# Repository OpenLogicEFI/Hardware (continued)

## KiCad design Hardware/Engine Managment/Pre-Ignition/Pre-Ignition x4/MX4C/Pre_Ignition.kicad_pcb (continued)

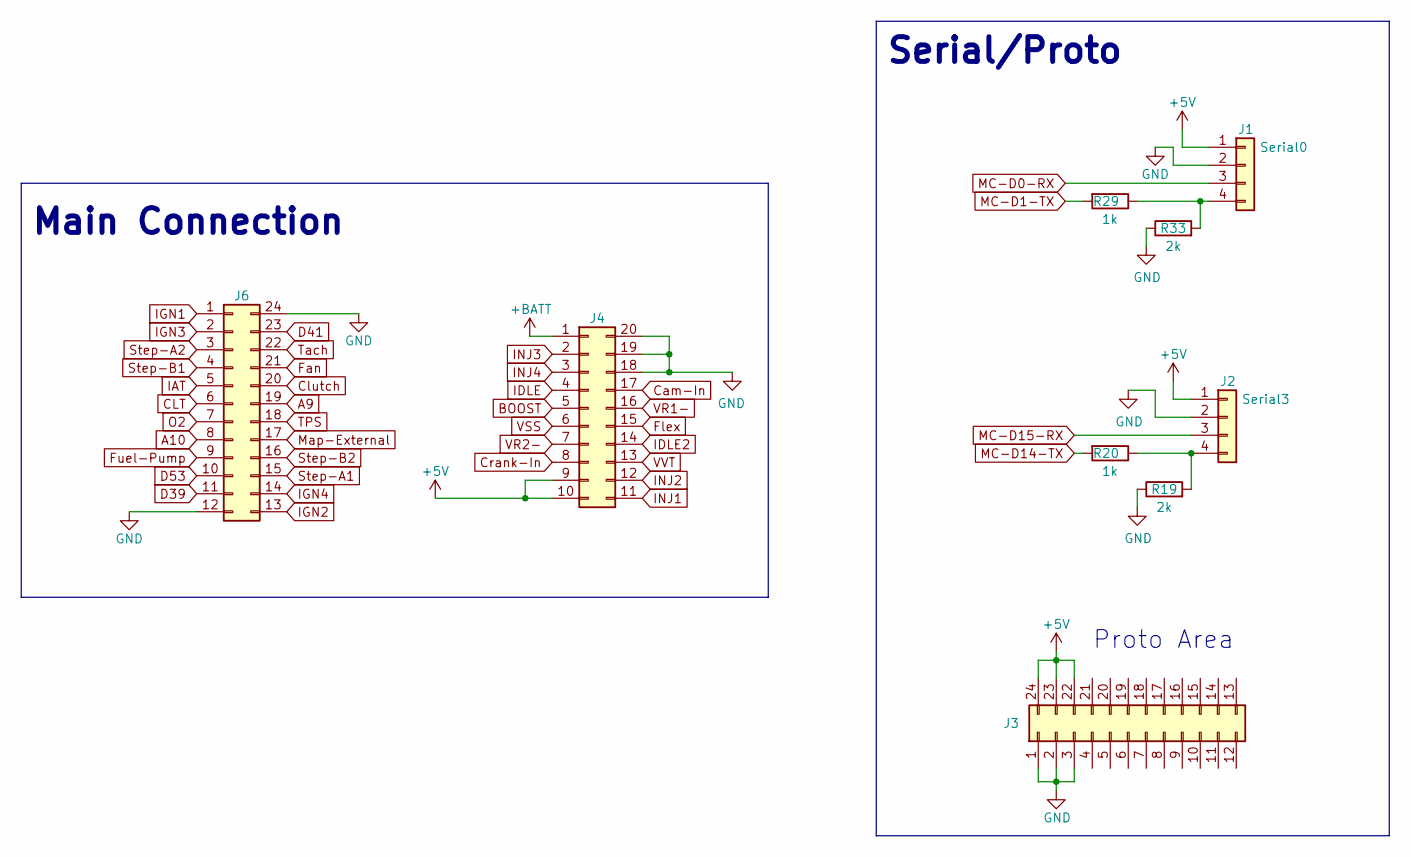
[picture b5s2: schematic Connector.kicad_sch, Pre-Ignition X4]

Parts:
J1: Serial0; 1X4-PROTO
J2: Serial3; 1X4-PROTO
J3: Conn_02x12_Counter_Clockwise; PROTO-3X8-24pin
J4: Conn_02x10_Counter_Clockwise; Molex_Micro-Fit_3.0_43045-2000_2x10_P3.00mm_Horizontal
J6: Conn_02x12_Counter_Clockwise; Molex_Micro-Fit_3.0_43045-2400_2x12_P3.00mm_Horizontal
R19, R33: 2k; R_0603_1608Metric; LCSC C22975
R20, R29: 1k; R_0603_1608Metric; LCSC C21190

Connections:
A9: J6.19; also elsewhere on the board
A10: J6.8; also elsewhere on the board
BOOST: J4.5; also elsewhere on the board
CLT: J6.6; also elsewhere on the board
Cam-In: J4.17; also elsewhere on the board
Clutch: J6.20; also elsewhere on the board
Crank-In: J4.8; also elsewhere on the board
D39: J6.11; also elsewhere on the board
D41: J6.23; also elsewhere on the board
D53: J6.10; also elsewhere on the board
Fan: J6.21; also elsewhere on the board
Flex: J4.15; also elsewhere on the board
Fuel-Pump: J6.9; also elsewhere on the board
IAT: J6.5; also elsewhere on the board
IDLE: J4.4; also elsewhere on the board
IDLE2: J4.14; also elsewhere on the board
IGN1: J6.1; also elsewhere on the board
IGN2: J6.13; also elsewhere on the board
IGN3: J6.2; also elsewhere on the board
IGN4: J6.14; also elsewhere on the board
INJ1: J4.11; also elsewhere on the board
INJ2: J4.12; also elsewhere on the board
INJ3: J4.2; also elsewhere on the board
INJ4: J4.3; also elsewhere on the board
MC-D0-RX: J1.3; also elsewhere on the board
MC-D1-TX: R29.2; also elsewhere on the board
MC-D14-TX: R20.2; also elsewhere on the board
MC-D15-RX: J2.3; also elsewhere on the board
Map-External: J6.17; also elsewhere on the board
unnamed: J1.4, R29.1, R33.2
unnamed: J2.4, R19.2, R20.1
O2: J6.7; also elsewhere on the board
Step-A1: J6.15; also elsewhere on the board
Step-A2: J6.3; also elsewhere on the board
Step-B1: J6.4; also elsewhere on the board
Step-B2: J6.16; also elsewhere on the board
TPS: J6.18; also elsewhere on the board
Tach: J6.22; also elsewhere on the board
VR1-: J4.16; also elsewhere on the board
VR2-: J4.7; also elsewhere on the board
VSS: J4.6; also elsewhere on the board

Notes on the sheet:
Proto Area
Serial/Proto
Main Connection

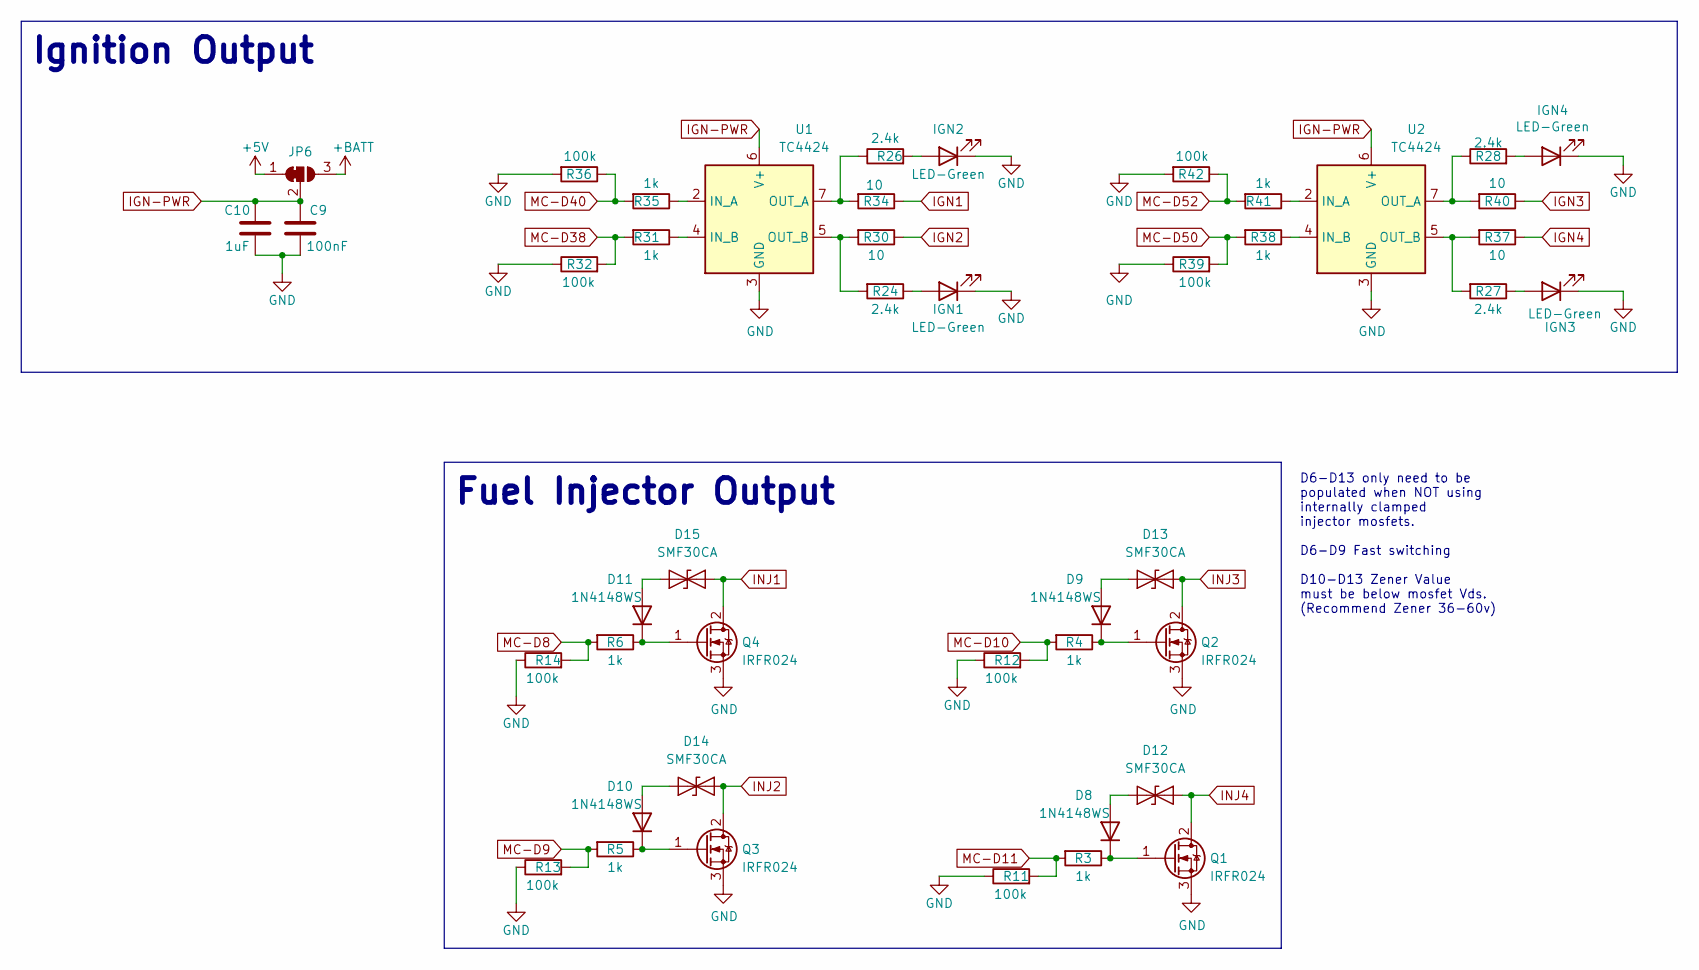
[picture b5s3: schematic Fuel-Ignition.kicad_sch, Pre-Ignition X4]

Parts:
C9: 100nF; C_0603_1608Metric; JLC C14663
C10: 1uF; C_0603_1608Metric; JLC C15849
D8, D9, D10, D11: 1N4148WS; D_SOD-323F; LCSC C2128
D12, D13, D14, D15: SMF30CA; D_SOD-123F
IGN1, IGN2, IGN3, IGN4: LED-Green; LED_0603_1608Metric; JLC C2286
JP6: SolderJumper_3_Bridged12; SolderJumper-3_P1.3mm_Bridged12_RoundedPad1.0x1.5mm_NumberL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
Q1, Q2, Q3, Q4: IRFR024; TO-252-2; LCSC C2583
R3, R4, R5, R6, R31, R35, R38, R41: 1k; R_0603_1608Metric; JLC C21190
R11, R12, R13, R14, R32, R36, R39, R42: 100k; R_0603_1608Metric; JLC C25803
R24, R27, R28: 2.4k; R_0603_1608Metric; JLC C22940
R26: 2.4k; R_0603_1608Metric; LCSC C22940
R30, R34, R37, R40: 10; R_1206_3216Metric; JLC C17561
U1, U2: TC4424; SOIC-8_3.9x4.9mm_P1.27mm; LCSC C2685358

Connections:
IGN1: R34.1; also elsewhere on the board
IGN2: R30.1; also elsewhere on the board
IGN3: R40.1; also elsewhere on the board
IGN4: R37.1; also elsewhere on the board
IGN-PWR: C9.1, C10.1, JP6.2 (C), U1.6 (V+), U2.6 (V+)
INJ1: D15.1 (A1), Q4.2 (D); also elsewhere on the board
INJ2: D14.1 (A1), Q3.2 (D); also elsewhere on the board
INJ3: D13.1 (A1), Q2.2 (D); also elsewhere on the board
INJ4: D12.1 (A1), Q1.2 (D); also elsewhere on the board
MC-D8: R6.2, R14.2; also elsewhere on the board
MC-D9: R5.2, R13.2; also elsewhere on the board
MC-D10: R4.2, R12.2; also elsewhere on the board
MC-D11: R3.2, R11.2; also elsewhere on the board
MC-D38: R31.2, R32.2; also elsewhere on the board
MC-D40: R35.2, R36.1; also elsewhere on the board
MC-D50: R38.2, R39.2; also elsewhere on the board
MC-D52: R41.2, R42.1; also elsewhere on the board
unnamed: D8.1 (K), Q1.1 (G), R3.1
unnamed: D9.1 (K), Q2.1 (G), R4.1
unnamed: D10.2 (A), D14.2 (A2)
unnamed: D10.1 (K), Q3.1 (G), R5.1
unnamed: D11.2 (A), D15.2 (A2)
unnamed: D11.1 (K), Q4.1 (G), R6.1
unnamed: D8.2 (A), D12.2 (A2)
unnamed: D9.2 (A), D13.2 (A2)
unnamed: IGN1.2 (A), R24.1
unnamed: IGN2.2 (A), R26.2
unnamed: IGN3.2 (A), R27.1
unnamed: IGN4.2 (A), R28.2
unnamed: R35.1, U1.2 (IN_A)
unnamed: R31.1, U1.4 (IN_B)
unnamed: R26.1, R34.2, U1.7 (OUT_A)
unnamed: R24.2, R30.2, U1.5 (OUT_B)
unnamed: R41.1, U2.2 (IN_A)
unnamed: R38.1, U2.4 (IN_B)
unnamed: R28.1, R40.2, U2.7 (OUT_A)
unnamed: R27.2, R37.2, U2.5 (OUT_B)

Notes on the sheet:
Fuel Injector Output
D6-D13 only need to be populated when NOT using internally clamped injector mosfets. D6-D9 Fast switching D10-D13 Zener Value must be below mosfet Vds. (Recommend Zener 36-60v)
Ignition Output

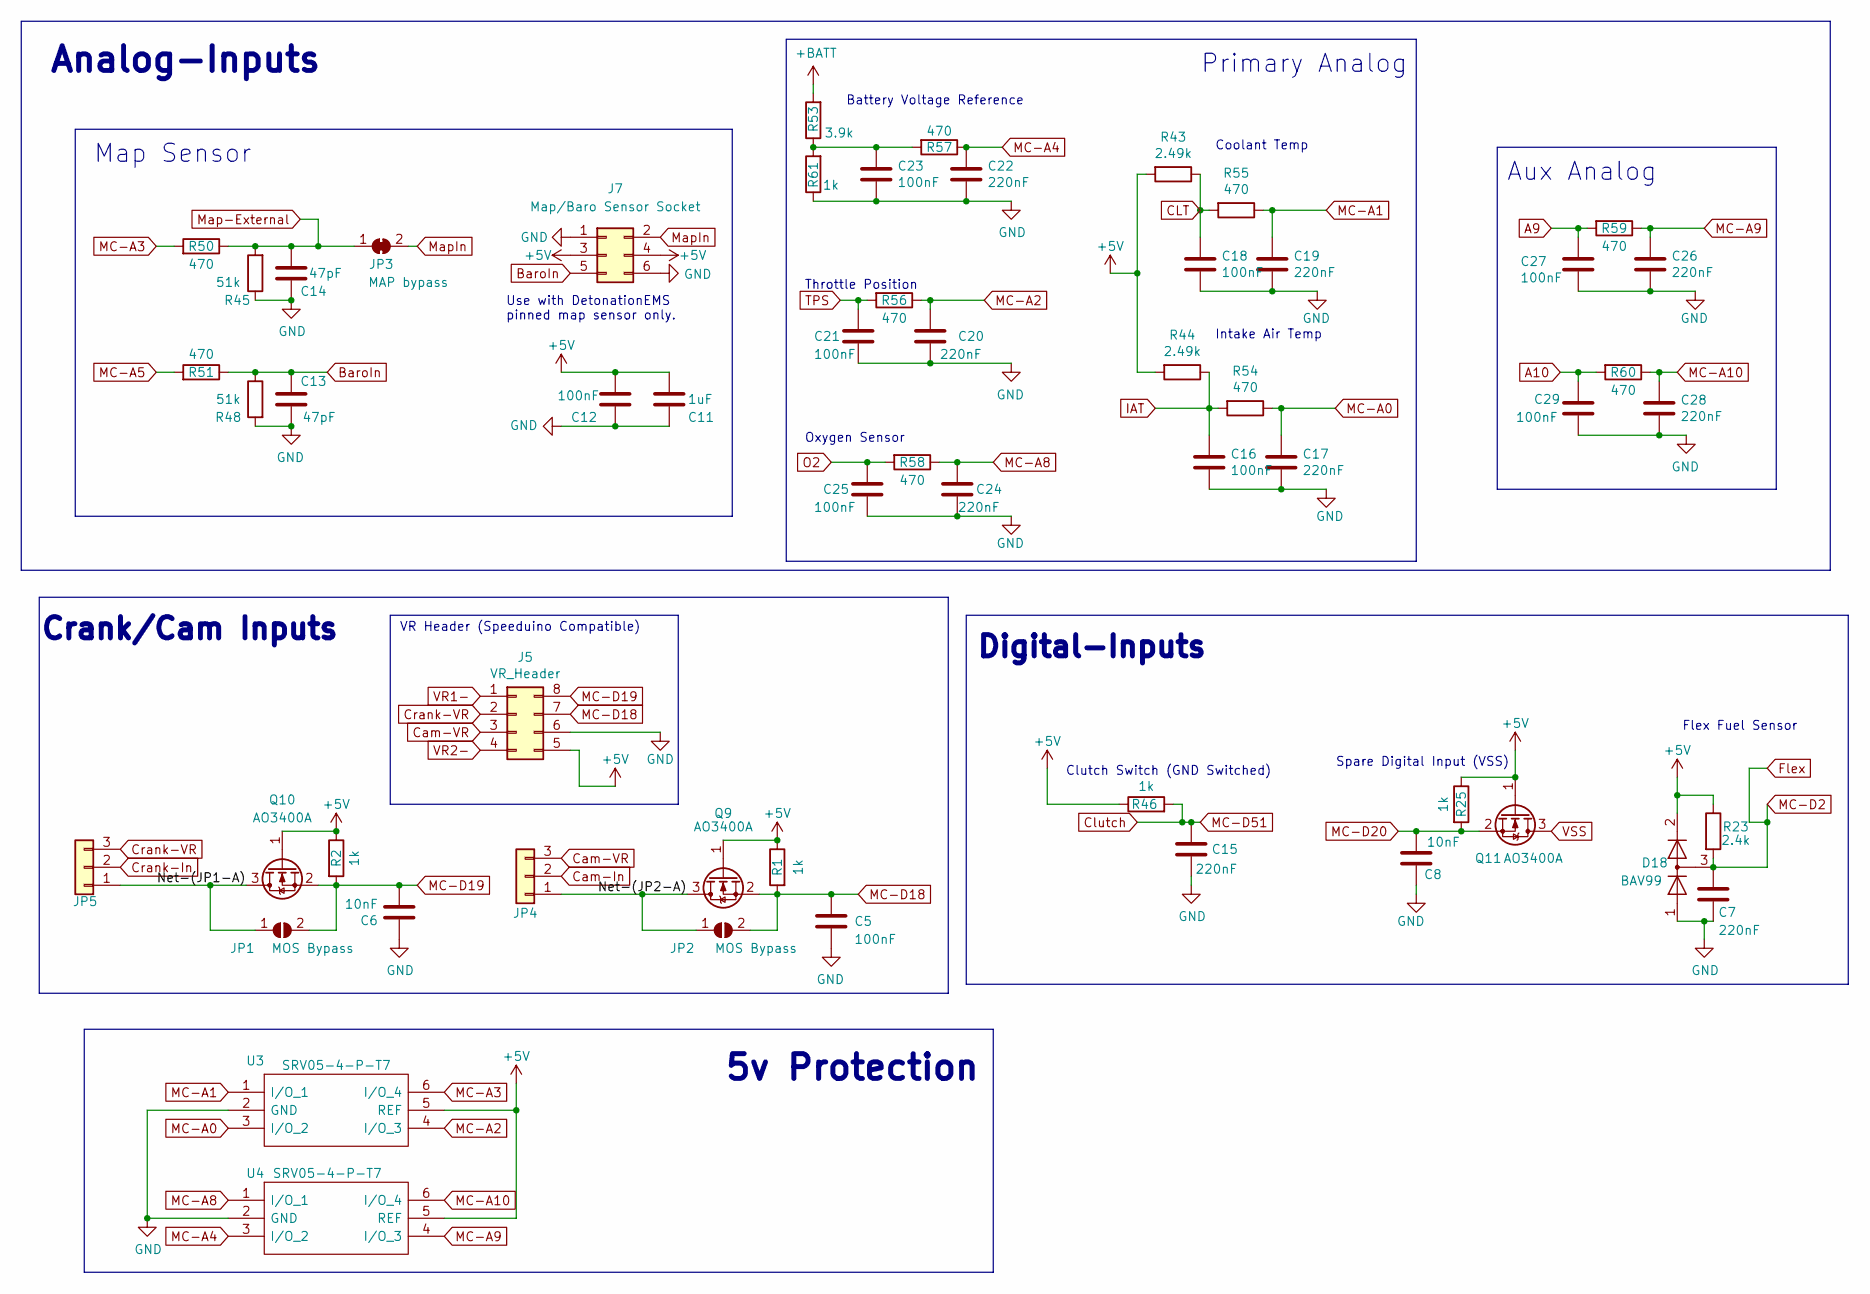
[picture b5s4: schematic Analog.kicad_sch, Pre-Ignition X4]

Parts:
C5, C12, C16, C18, C21, C23, C25, C27, C29: 100nF; C_0603_1608Metric; JLC C14663
C6, C8: 10nF; C_0603_1608Metric; JLC C57112
C7, C15, C17, C19, C20, C22, C24, C26, C28: 220nF; C_0603_1608Metric; JLC C5378
C11: 1uF; C_0603_1608Metric; JLC C15849
C13, C14: 47pF; C_0603_1608Metric; LCSC C1671
D18: BAV99; SOT-23; LCSC C2500
J5: VR_Header; Socket_VRConditioner_Corrected
J7: Map/Baro Sensor Socket; PinSocket_2x03_P2.54mm_Vertical
JP1, JP2: MOS Bypass; SolderJumper-2_P1.3mm_Open_RoundedPad1.0x1.5mm
JP3: MAP bypass; SolderJumper-2_P1.3mm_Bridged_RoundedPad1.0x1.5mm
JP4, JP5: Conn_01x03; 1x03-Proto
Q9, Q10, Q11: AO3400A; SOT-23; LCSC C20917
R1, R2, R25, R46, R61: 1k; R_0603_1608Metric; JLC C21190
R23: 2.4k; R_0603_1608Metric; JLC C22940
R43, R44: 2.49k; R_Axial_DIN0207_L6.3mm_D2.5mm_P7.62mm_Horizontal
R45, R48: 51k; R_0603_1608Metric; JLC C23196
R50, R51, R54, R55, R56, R57, R58, R59, R60: 470; R_0603_1608Metric; JLC C23179
R53: 3.9k; R_0603_1608Metric; JLC C23018
U3, U4: SRV05-4-P-T7; SOT-23-6; JLC C85364

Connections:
/Inputs/Net-(JP1-A): JP1.1 (A), JP5.1, Q10.3 (D)
/Inputs/Net-(JP2-A): JP2.1 (A), JP4.1, Q9.3 (D)
A9: C27.1, R59.2; also elsewhere on the board
A10: C29.1, R60.2; also elsewhere on the board
BaroIn: C13.1, J7.5, R48.1, R51.1
CLT: C18.1, R43.1, R55.2; also elsewhere on the board
Cam-In: JP4.2; also elsewhere on the board
Cam-VR: J5.3, JP4.3
Clutch: C15.1, R46.2; also elsewhere on the board
Crank-In: JP5.2; also elsewhere on the board
Crank-VR: J5.2, JP5.3
Flex: C7.1, D18.3 (K), R23.2; also elsewhere on the board
IAT: C16.1, R44.1, R54.2; also elsewhere on the board
MC-A0: C17.1, R54.1, U3.3 (I/O_2); also elsewhere on the board
MC-A1: C19.1, R55.1, U3.1 (I/O_1); also elsewhere on the board
MC-A2: C20.1, R56.1, U3.4 (I/O_3); also elsewhere on the board
MC-A3: R50.2, U3.6 (I/O_4); also elsewhere on the board
MC-A4: C22.1, R57.1, U4.3 (I/O_2); also elsewhere on the board
MC-A5: R51.2; also elsewhere on the board
MC-A8: C24.1, R58.1, U4.1 (I/O_1); also elsewhere on the board
MC-A9: C26.1, R59.1, U4.4 (I/O_3); also elsewhere on the board
MC-A10: C28.1, R60.1, U4.6 (I/O_4); also elsewhere on the board
MC-D18: C5.2, J5.7, JP2.2 (B), Q9.2 (S), R1.2; also elsewhere on the board
MC-D19: C6.2, J5.8, JP1.2 (B), Q10.2 (S), R2.2; also elsewhere on the board
MC-D20: C8.1, Q11.2 (S), R25.2; also elsewhere on the board
Map-External: C14.1, JP3.1 (A), R45.2, R50.1; also elsewhere on the board
MapIn: J7.2, JP3.2 (B)
unnamed: C23.1, R53.1, R57.2, R61.2
O2: C25.1, R58.2; also elsewhere on the board
TPS: C21.1, R56.2; also elsewhere on the board
VR1-: J5.1; also elsewhere on the board
VR2-: J5.4; also elsewhere on the board
VSS: Q11.3 (D); also elsewhere on the board

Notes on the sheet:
Aux Analog
Map Sensor
Throttle Position
Clutch Switch (GND Switched)
Crank/Cam Inputs
Analog-Inputs
Oxygen Sensor
Primary Analog
Coolant Temp
Intake Air Temp
VR Header (Speeduino Compatible)
Battery Voltage Reference
Spare Digital Input (VSS)
Use with DetonationEMS pinned map sensor only.
Flex Fuel Sensor
5v Protection
Digital-Inputs

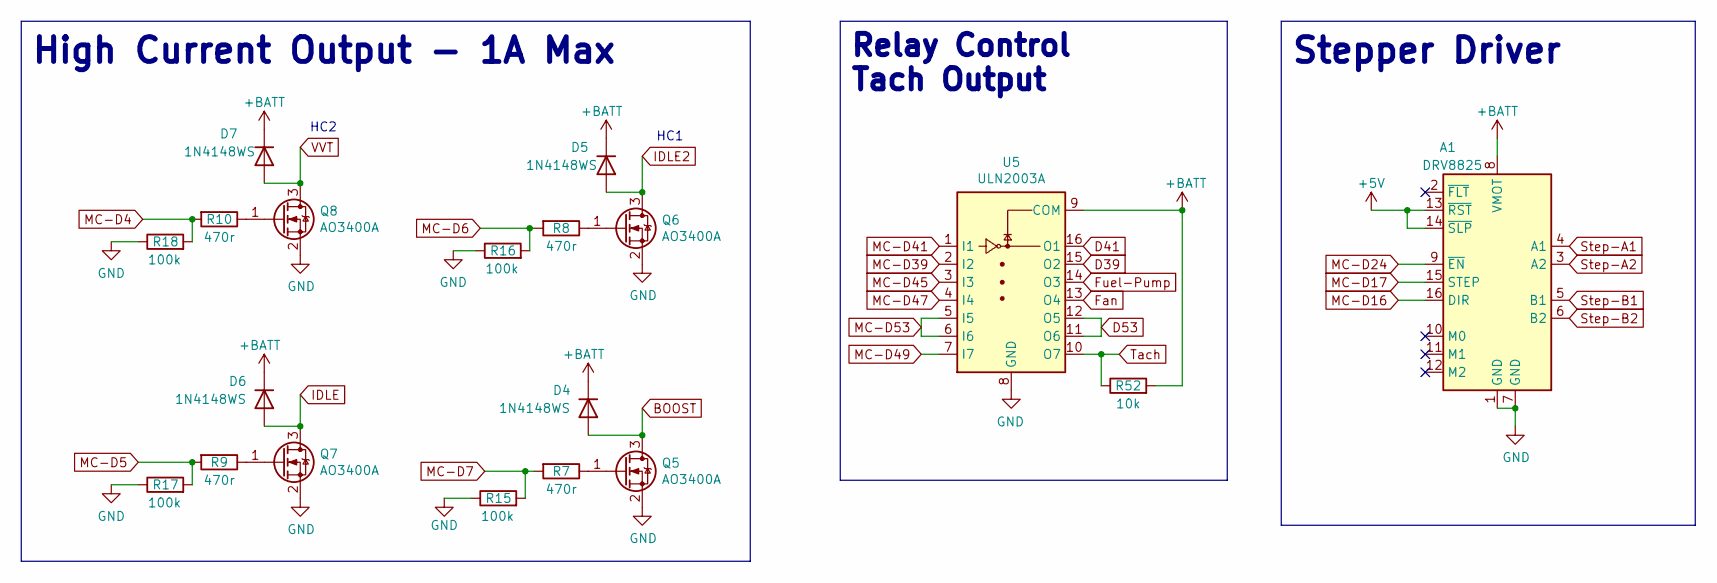
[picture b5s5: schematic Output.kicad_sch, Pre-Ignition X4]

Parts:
A1: DRV8825; DVR8825-Labeled-Front
D4, D5, D6, D7: 1N4148WS; D_SOD-323F; JLC C2128
Q5, Q6, Q7, Q8: AO3400A; SOT-23; JLC C20917
R7, R8, R9, R10: 470r; R_0402_1005Metric; LCSC C25117
R15, R16, R17, R18: 100k; R_0603_1608Metric; LCSC C25803
R52: 10k; R_0603_1608Metric; LCSC C25804
U5: ULN2003A; SOIC-16_3.9x9.9mm_P1.27mm; JLC C7512

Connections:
BOOST: D4.2 (A), Q5.3 (D); also elsewhere on the board
D39: U5.15 (O2); also elsewhere on the board
D41: U5.16 (O1); also elsewhere on the board
D53: U5.11 (O6), U5.12 (O5); also elsewhere on the board
Fan: U5.13 (O4); also elsewhere on the board
Fuel-Pump: U5.14 (O3); also elsewhere on the board
IDLE: D6.2 (A), Q7.3 (D); also elsewhere on the board
IDLE2: D5.2 (A), Q6.3 (D); also elsewhere on the board
MC-D4: R10.2, R18.2; also elsewhere on the board
MC-D5: R9.2, R17.2; also elsewhere on the board
MC-D7: R7.2, R15.2; also elsewhere on the board
MC-D16: A1.16 (DIR); also elsewhere on the board
MC-D17: A1.15 (STEP); also elsewhere on the board
MC-D24: A1.9 (~EN); also elsewhere on the board
MC-D39: U5.2 (I2); also elsewhere on the board
MC-D41: U5.1 (I1); also elsewhere on the board
MC-D45: U5.3 (I3); also elsewhere on the board
MC-D47: U5.4 (I4); also elsewhere on the board
MC-D49: U5.7 (I7); also elsewhere on the board
MC-D53: U5.5 (I5), U5.6 (I6); also elsewhere on the board
unnamed: Q5.1 (G), R7.1
unnamed: Q7.1 (G), R9.1
unnamed: Q8.1 (G), R10.1
Step-A1: A1.4 (A1); also elsewhere on the board
Step-A2: A1.3 (A2); also elsewhere on the board
Step-B1: A1.5 (B1); also elsewhere on the board
Step-B2: A1.6 (B2); also elsewhere on the board
Tach: R52.1, U5.10 (O7); also elsewhere on the board

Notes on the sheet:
High Current Output - 1A Max
HC2
HC1
Relay Control Tach Output
Stepper Driver

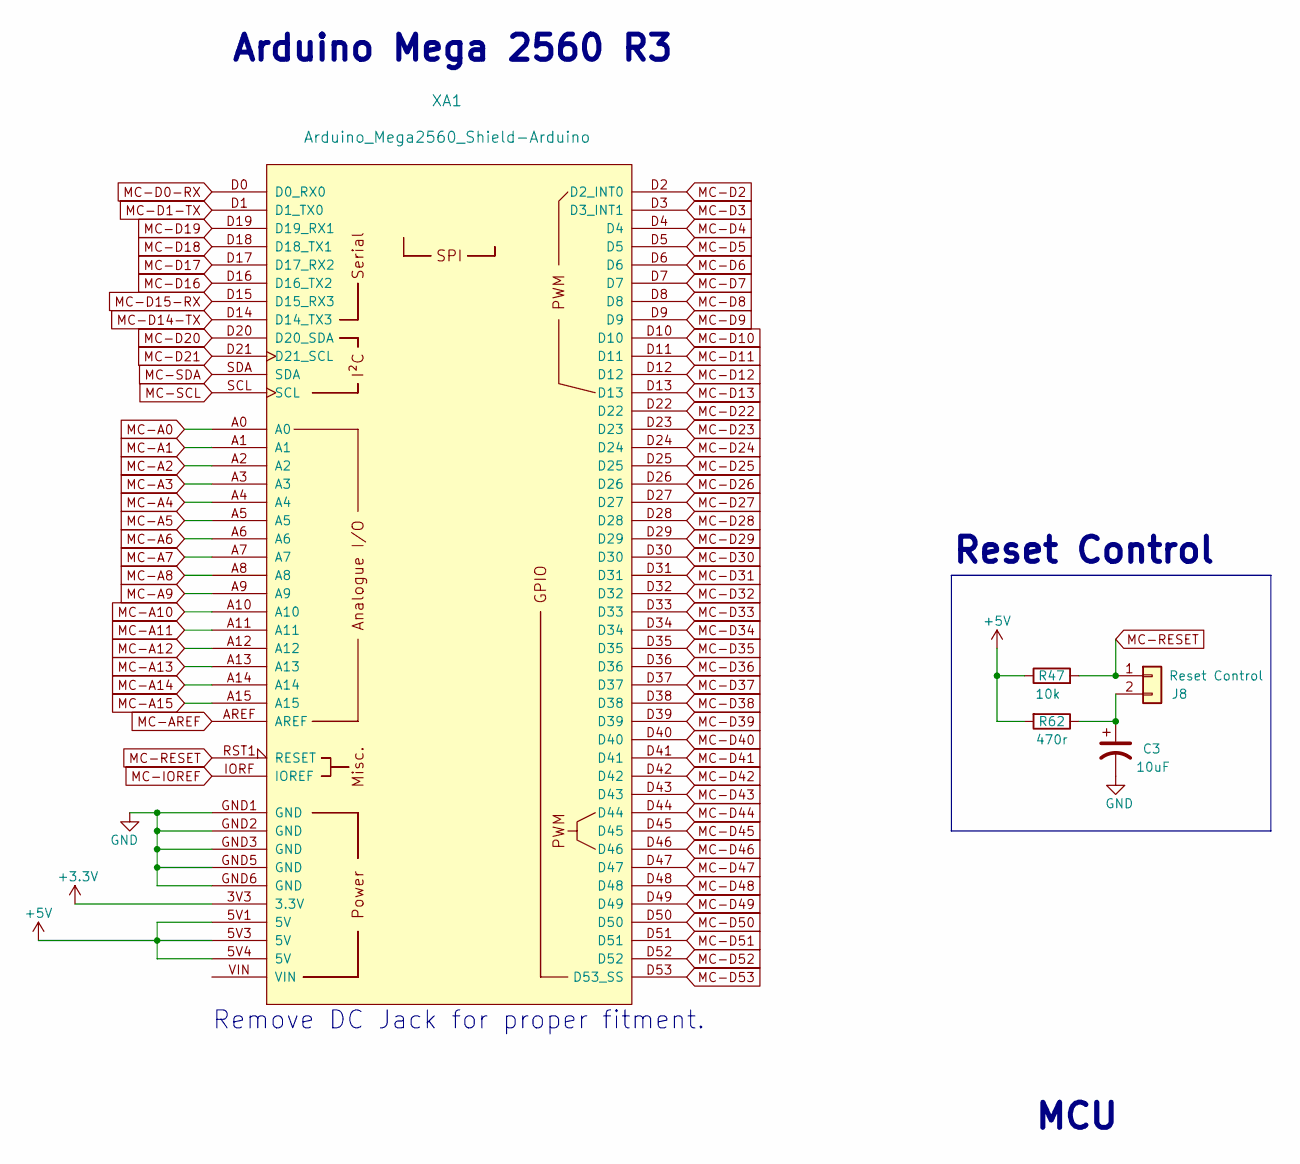
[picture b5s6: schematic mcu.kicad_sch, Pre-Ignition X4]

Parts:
C3: 10uF; CP_EIA-3216-18_Kemet-A; Manufacture Part Number TAJA106K016RNJ; LCSC C7171
J8: Reset Control; 1x02-Proto
R47: 10k; R_0603_1608Metric; LCSC C25804
R62: 470r; R_0402_1005Metric; LCSC C25117
XA1: Arduino_Mega2560_Shield-Arduino; Arduino-Mega2560-Shield-Speeduino

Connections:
+3V3: XA1.3V3 (3.3V)
Clutch: XA1.D51; also elsewhere on the board
Flex: XA1.D2 (D2_INT0); also elsewhere on the board
MC-A0: XA1.A0; also elsewhere on the board
MC-A1: XA1.A1; also elsewhere on the board
MC-A2: XA1.A2; also elsewhere on the board
MC-A3: XA1.A3; also elsewhere on the board
MC-A4: XA1.A4; also elsewhere on the board
MC-A5: XA1.A5; also elsewhere on the board
MC-A6: XA1.A6
MC-A7: XA1.A7
MC-A8: XA1.A8; also elsewhere on the board
MC-A9: XA1.A9; also elsewhere on the board
MC-A10: XA1.A10; also elsewhere on the board
MC-A11: XA1.A11
MC-A12: XA1.A12
MC-A13: XA1.A13
MC-A14: XA1.A14
MC-A15: XA1.A15
MC-AREF: XA1.AREF
MC-D0-RX: XA1.D0 (D0_RX0); also elsewhere on the board
MC-D1-TX: XA1.D1 (D1_TX0); also elsewhere on the board
MC-D3: XA1.D3 (D3_INT1)
MC-D4: XA1.D4; also elsewhere on the board
MC-D5: XA1.D5; also elsewhere on the board
MC-D7: XA1.D7; also elsewhere on the board
MC-D8: XA1.D8; also elsewhere on the board
MC-D9: XA1.D9; also elsewhere on the board
MC-D10: XA1.D10; also elsewhere on the board
MC-D11: XA1.D11; also elsewhere on the board
MC-D12: XA1.D12
MC-D13: XA1.D13
MC-D14-TX: XA1.D14 (D14_TX3); also elsewhere on the board
MC-D15-RX: XA1.D15 (D15_RX3); also elsewhere on the board
MC-D16: XA1.D16 (D16_TX2); also elsewhere on the board
MC-D17: XA1.D17 (D17_RX2); also elsewhere on the board
MC-D18: XA1.D18 (D18_TX1); also elsewhere on the board
MC-D19: XA1.D19 (D19_RX1); also elsewhere on the board
MC-D20: XA1.D20 (D20_SDA); also elsewhere on the board
MC-D21: XA1.D21 (D21_SCL)
MC-D22: XA1.D22
MC-D23: XA1.D23
MC-D24: XA1.D24; also elsewhere on the board
MC-D25: XA1.D25
MC-D26: XA1.D26
MC-D27: XA1.D27
MC-D28: XA1.D28
MC-D29: XA1.D29
MC-D30: XA1.D30
MC-D31: XA1.D31
MC-D32: XA1.D32
MC-D33: XA1.D33
MC-D34: XA1.D34
MC-D35: XA1.D35
MC-D36: XA1.D36
MC-D37: XA1.D37
MC-D38: XA1.D38; also elsewhere on the board
MC-D39: XA1.D39; also elsewhere on the board
MC-D40: XA1.D40; also elsewhere on the board
MC-D41: XA1.D41; also elsewhere on the board
MC-D42: XA1.D42
MC-D43: XA1.D43
MC-D44: XA1.D44
MC-D45: XA1.D45; also elsewhere on the board
MC-D46: XA1.D46
MC-D47: XA1.D47; also elsewhere on the board
MC-D48: XA1.D48
MC-D49: XA1.D49; also elsewhere on the board
MC-D50: XA1.D50; also elsewhere on the board
MC-D52: XA1.D52; also elsewhere on the board
MC-D53: XA1.D53 (D53_SS); also elsewhere on the board
MC-IOREF: XA1.IORF (IOREF)
MC-RESET: J8.1, R47.2, XA1.RST1 (RESET)
MC-SCL: XA1.SCL
MC-SDA: XA1.SDA

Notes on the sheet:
Remove DC Jack for proper fitment.
Reset Control
MCU
Arduino Mega 2560 R3

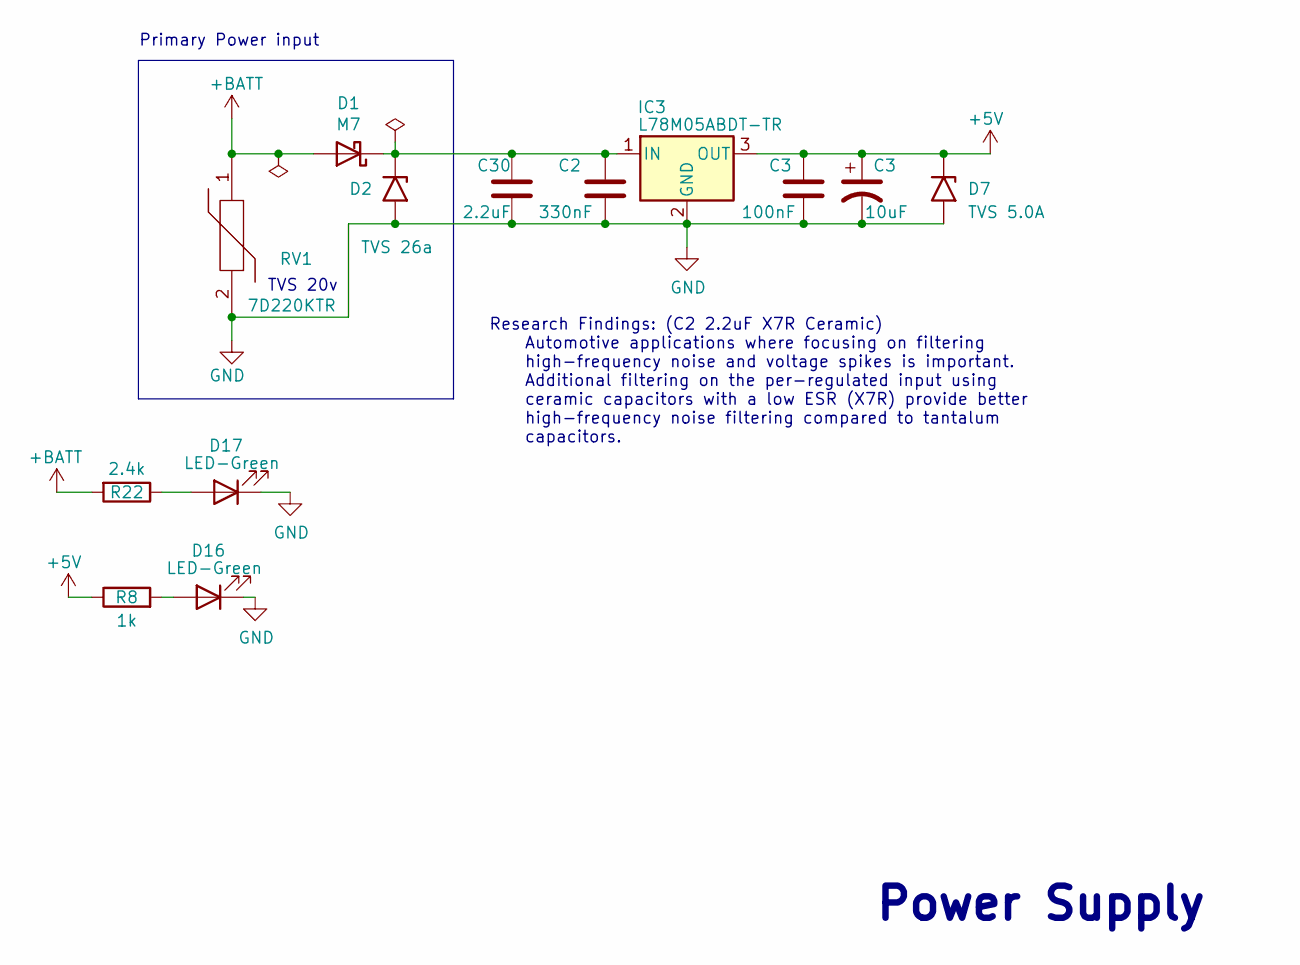
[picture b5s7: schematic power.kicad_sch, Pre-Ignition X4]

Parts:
C2: 330nF; C_0805_2012Metric; Manufacture Part Number 0805B334K500NT; LCSC C1740
C3: 10uF; CP_EIA-3216-18_Kemet-A; Manufacture Part Number TAJA106K016RNJ; LCSC C7171
C30: 2.2uF; C_1206_3216Metric; Manufacture Part Number CL31B225KBHNNNE; LCSC C50254
D1: M7; D_SMA; Manufacture Part Number M7; LCSC C95872
D2: TVS 26a; D_SMA; Manufacture Part Number SMAJ26A; LCSC C3001962
D7: TVS 5.0A; D_SMA; Manufacture Part Number SMAJ5.0A; LCSC C2925443
D16, D17: LED-Green; LED_0603_1608Metric; LCSC C72043
IC3: L78M05ABDT-TR; TO-252-2-Thermal; Manufacture Part Number L78M05ABDT-TR; LCSC C58069
R8: 1k; R_0603_1608Metric; JLC C21190
R22: 2.4k; R_0603_1608Metric; LCSC C22940
RV1: 7D220KTR; MOV07D220KTR

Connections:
unnamed 106: C2.1, D1.1 (K), D2.1 (A1); also elsewhere on the board
unnamed: D17.2 (A), R22.1

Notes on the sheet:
Primary Power input
TVS 20v
Research Findings: (C2 2.2uF X7R Ceramic) Automotive applications where focusing on filtering high-frequency noise and voltage spikes is important. Additional filtering on the per-regulated input using ceramic capacitors with a low ESR (X7R) provide better high-frequency noise filtering compared to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
Power Supply

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
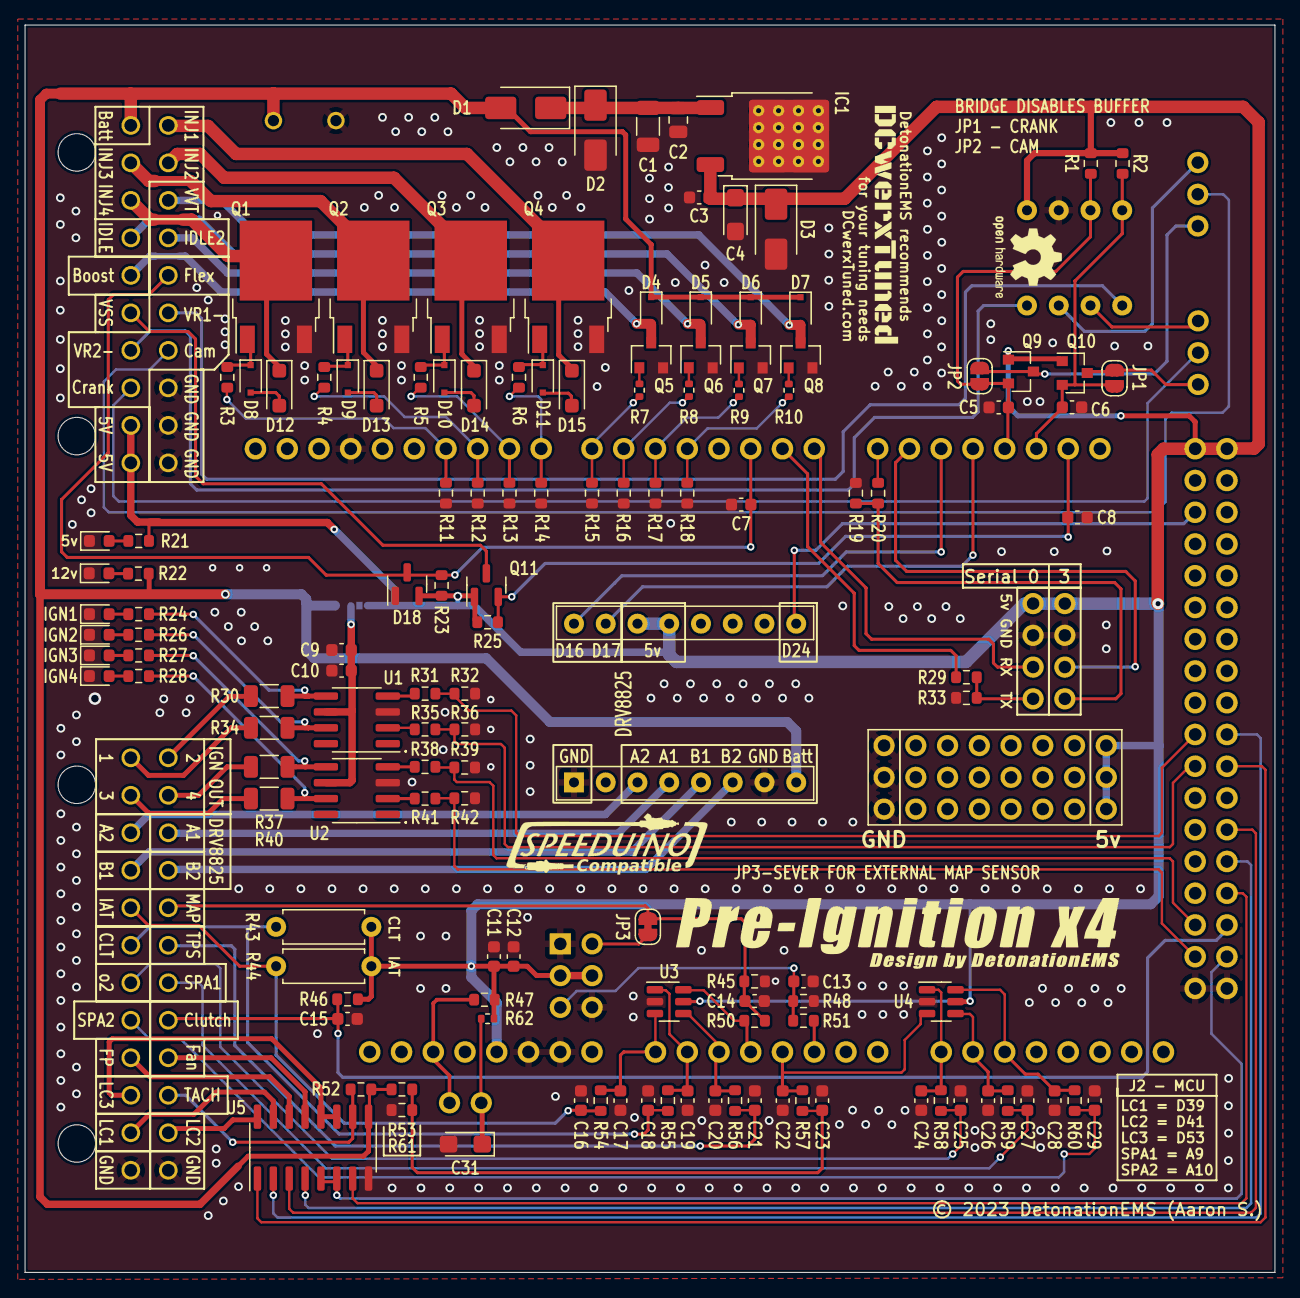
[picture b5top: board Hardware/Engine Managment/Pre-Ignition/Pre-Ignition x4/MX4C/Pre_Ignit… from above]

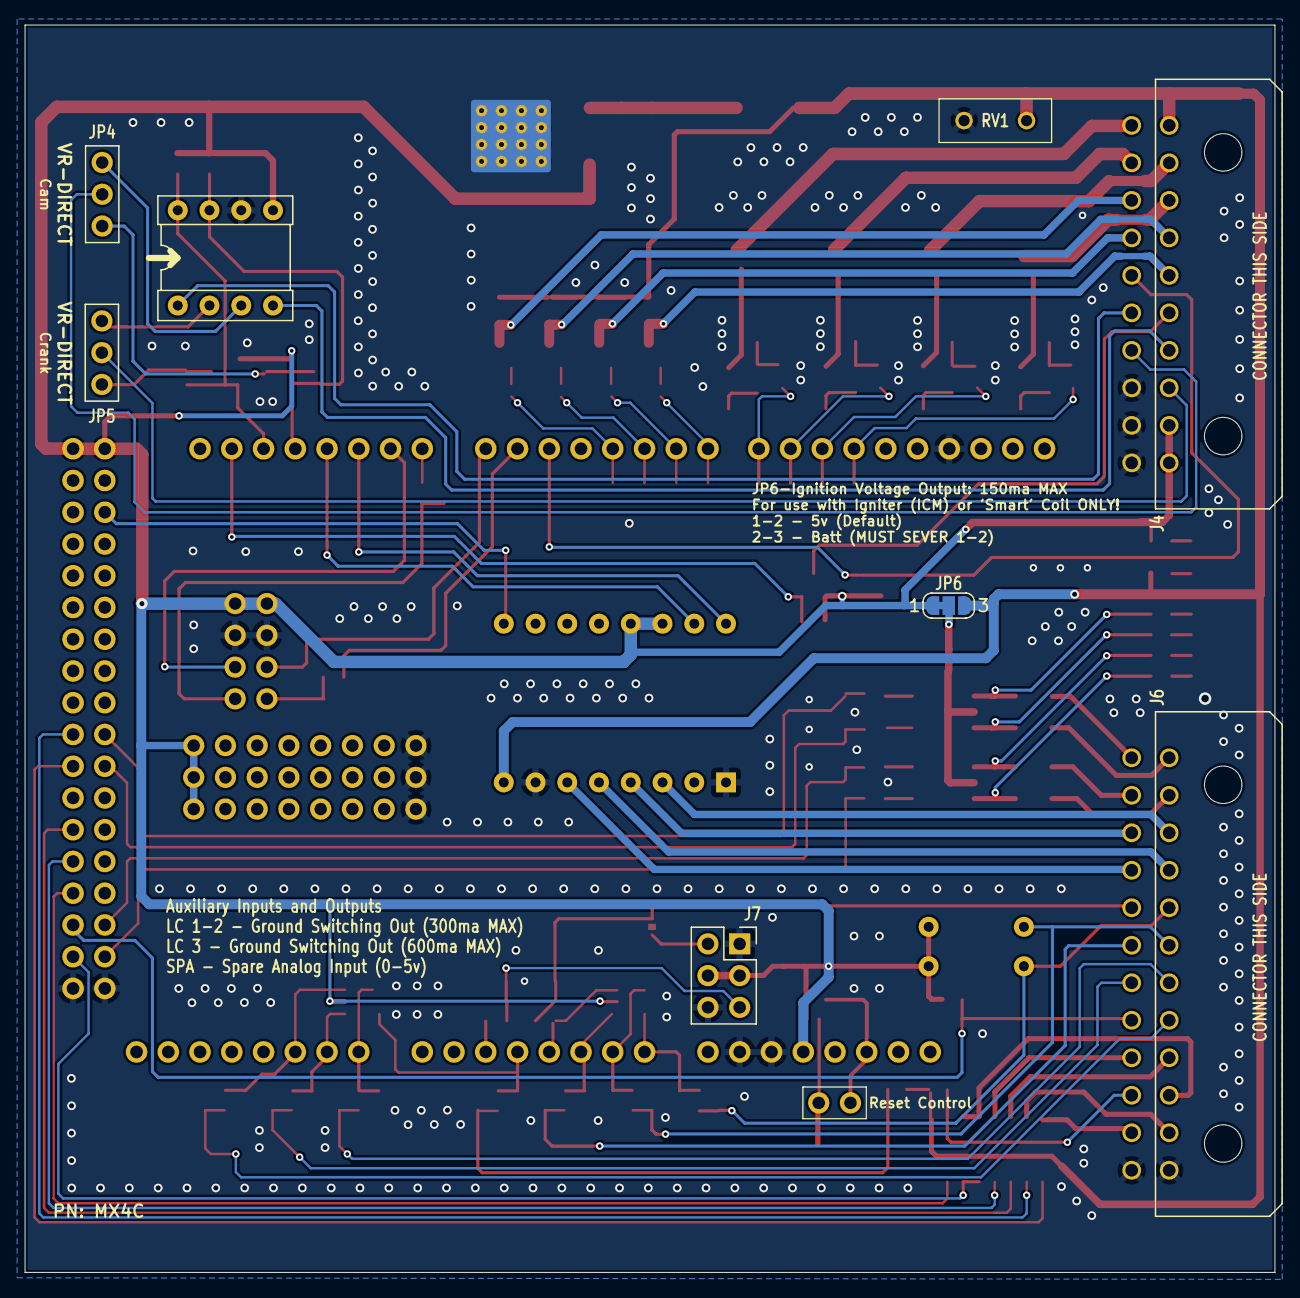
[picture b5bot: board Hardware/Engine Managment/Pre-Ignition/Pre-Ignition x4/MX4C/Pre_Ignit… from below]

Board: 2 copper layers, 100.0 x 99.8 mm, 152 parts (9 on the bottom side), 115 nets.

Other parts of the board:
C1: 2.2uF; C_1206_3216Metric
C4, C31: 10uF; CP_EIA-3216-18_Kemet-A
D3: TVS 5.0A; D_SMA
G1: DCWERX; DCWerx-19mm
G2: OSHW-Logo2_7.3x6mm_SilkScreen
G3: LOGO; SpeeduinoCompatible-17mm
G4: Pre-Ignition; Pre-IgnitionX4-35mm
G5: DESIGN; Design by 20mm
IC1: L78M05ABDT-TR; TO-252-2-Thermal
R21: 1k; R_0603_1608Metric

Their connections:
unnamed 106: C1.1, IC1.1 (IN); also elsewhere on the board
